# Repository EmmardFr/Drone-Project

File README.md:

# Drone-Project

- `hardware/` contains hardware design files:
  - `Datasheets/`: component datasheets (IMUs, barometers, and related parts) used during hardware selection.
  - `Graphics/`: project graphics and visual assets.
  - `Schematics/`: standalone schematic libraries/references for key components (e.g., sensors and Teensy 4.1).
  - PCB designs, in development order:
    1. `ismd_flight_computer (obselete)/` (deprecated early prototype): initial all-in-one flight-computer concept combining Teensy 4.1, multiple IMU/barometer options, and onboard power circuitry.
    2. `ismd_fc_sensortest/`: dedicated sensor test board used to compare multiple IMU and barometer options around a Teensy 4.1 base.
    3. `Carrier_PCB/`: first carrier board revision for system integration (power distribution, receiver I/O, ESC/motor signal breakout, and module connectors).
    4. `Carrier_PCB_v2/`: second carrier board revision refining the carrier design and production-ready outputs.
- `software/` contains firmware, libraries, and software tooling.

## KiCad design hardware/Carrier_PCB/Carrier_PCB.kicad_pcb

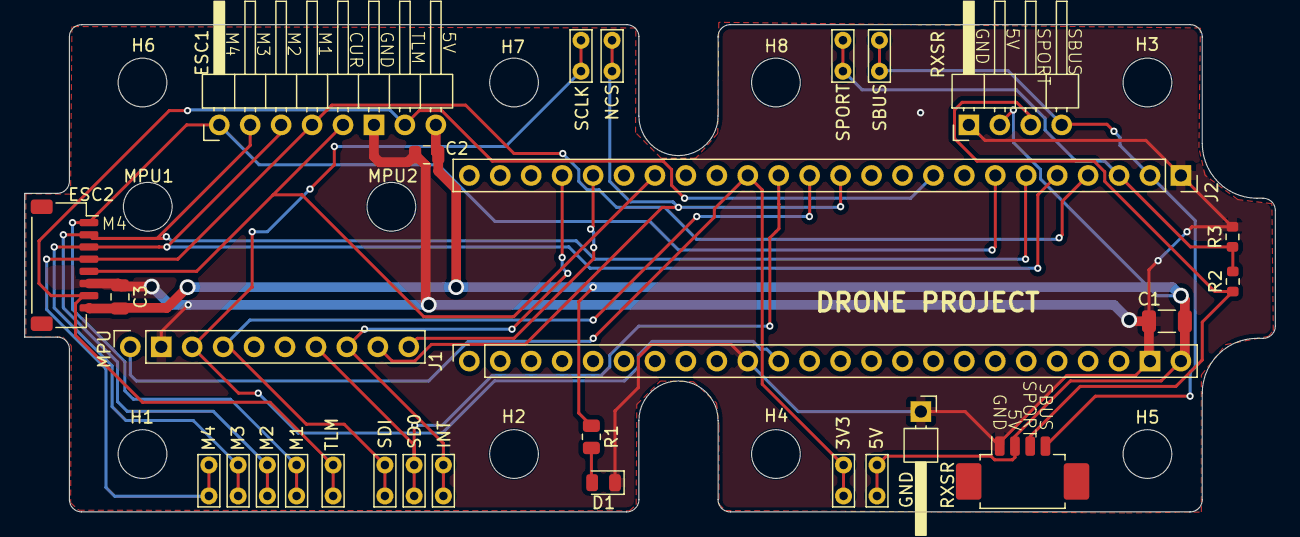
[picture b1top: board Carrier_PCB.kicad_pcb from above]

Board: 2 copper layers, 102.7 x 40.0 mm, 39 parts (0 on the bottom side), 19 nets.

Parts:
3V3, 5V: TestPoint; TestPoint_Bridge_Pitch2.54mm_Drill0.7mm
C1: 10u; C_1206_3216Metric
C2, C3: 100n; C_0805_2012Metric
D1: LED; LED_0805_2012Metric
ESC1: Conn_01x08; PinHeader_1x08_P2.54mm_Horizontal
ESC2: Conn_01x08; JST_SH_SM08B-SRSS-TB_1x08-1MP_P1.00mm_Horizontal
GND: Conn_01x01; PinHeader_1x01_P2.54mm_Horizontal
H1, H2, H3, H4, H5, H6, H7, H8: MountingHole; MountingHole_4mm
INT: TestPoint; TestPoint_Bridge_Pitch2.54mm_Drill0.7mm
J1, J2: Conn_01x24; PinSocket_1x24_P2.54mm_Vertical
M1, M2, M3, M4: TestPoint; TestPoint_Bridge_Pitch2.54mm_Drill0.7mm
MPU: Conn_01x10; PinSocket_1x10_P2.54mm_Vertical
MPU1, MPU2: MountingHole; MountingHole_4mm
NCS: TestPoint; TestPoint_Bridge_Pitch2.54mm_Drill0.7mm
R1: 300; R_0805_2012Metric
R2: 10K; R_0603_1608Metric
R3: 20K; R_0603_1608Metric
RXSR: Conn_01x04; PinHeader_1x04_P2.54mm_Horizontal
RXSR#2: Conn_01x04; Molex_PicoBlade_53261-0471_1x04-1MP_P1.25mm_Horizontal
SBUS: TestPoint; TestPoint_Bridge_Pitch2.54mm_Drill0.7mm
SCLK: TestPoint; TestPoint_Bridge_Pitch2.54mm_Drill0.7mm
SD0: TestPoint; TestPoint_Bridge_Pitch2.54mm_Drill0.7mm
SDI: TestPoint; TestPoint_Bridge_Pitch2.54mm_Drill0.7mm
SPORT: TestPoint; TestPoint_Bridge_Pitch2.54mm_Drill0.7mm
TLM: TestPoint; TestPoint_Bridge_Pitch2.54mm_Drill0.7mm

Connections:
+3.3V: 3V3.1 (1_1), J2.15, MPU.1
+5V: 5V.1 (1_1), C1.1, C2.2, C3.2, ESC1.8, ESC2.8, J1.24, R1.1, RXSR.2, RXSR#2.2
GND: C1.2, C2.1, C3.1, D1.1 (K), ESC1.6, ESC2.6, GND.1 (Pin_1_1), J1.10, J1.23, J2.1, MPU.2, R3.2, RXSR.1, RXSR#2.1
unnamed: D1.2 (A), R1.2
unnamed: J1.11, MPU.3, SCLK.1 (1_1)
unnamed: J2.2, RXSR.4, RXSR#2.4, SBUS.1 (1_1)
unnamed: ESC1.4, ESC2.4, J2.4, M4.1 (1_1)
unnamed: ESC1.3, ESC2.3, J2.5, M3.1 (1_1)
unnamed: ESC1.2, ESC2.2, J2.6, M2.1 (1_1)
unnamed: ESC1.1, ESC2.1, J2.7, M1.1 (1_1)
unnamed: ESC1.7, ESC2.7, J2.9, TLM.1 (1_1)
unnamed: J2.12, MPU.9, NCS.1 (1_1)
unnamed: J2.13, MPU.4, SDI.1 (1_1)
unnamed: J2.14, MPU.7, SD0.1 (1_1)
unnamed: ESC1.5, ESC2.5, J2.18
unnamed: J2.20, MPU.10
unnamed: INT.1 (1_1), J2.21, MPU.8
SPORT_MCU: J2.3, R2.2, R3.1, SPORT.1 (1_1)
SPORT_RX: R2.1, RXSR.3, RXSR#2.3

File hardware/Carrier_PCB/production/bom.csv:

Designator,Footprint,Quantity,Value,LCSC Part #
"3V3, 5V, INT, M1, M2, M3, M4, NCS, SBUS, SCLK, SD0, SDI, SPORT, TLM",TestPoint_Bridge_Pitch2.54mm_Drill0.7mm,14,TestPoint,
C1,1206,1,10u,
"C2, C3",0805,2,100n,
D1,0805,1,LED,
ESC1,PinHeader_1x08_P2.54mm_Horizontal,1,Conn_01x08,
ESC2,JST_SH_SM08B-SRSS-TB_1x08-1MP_P1.00mm_Horizontal,1,Conn_01x08,
GND,PinHeader_1x01_P2.54mm_Horizontal,1,Conn_01x01,
"J1, J2",PinSocket_1x24_P2.54mm_Vertical,2,Conn_01x24,
MPU,PinSocket_1x10_P2.54mm_Vertical,1,Conn_01x10,
R1,0805,1,300,
R2,0603,1,10K,
R3,0603,1,20K,
RXSR_2,Molex_PicoBlade_53261-0471_1x04-1MP_P1.25mm_Horizontal,1,Conn_01x04,
RXSR,PinHeader_1x04_P2.54mm_Horizontal,1,Conn_01x04,

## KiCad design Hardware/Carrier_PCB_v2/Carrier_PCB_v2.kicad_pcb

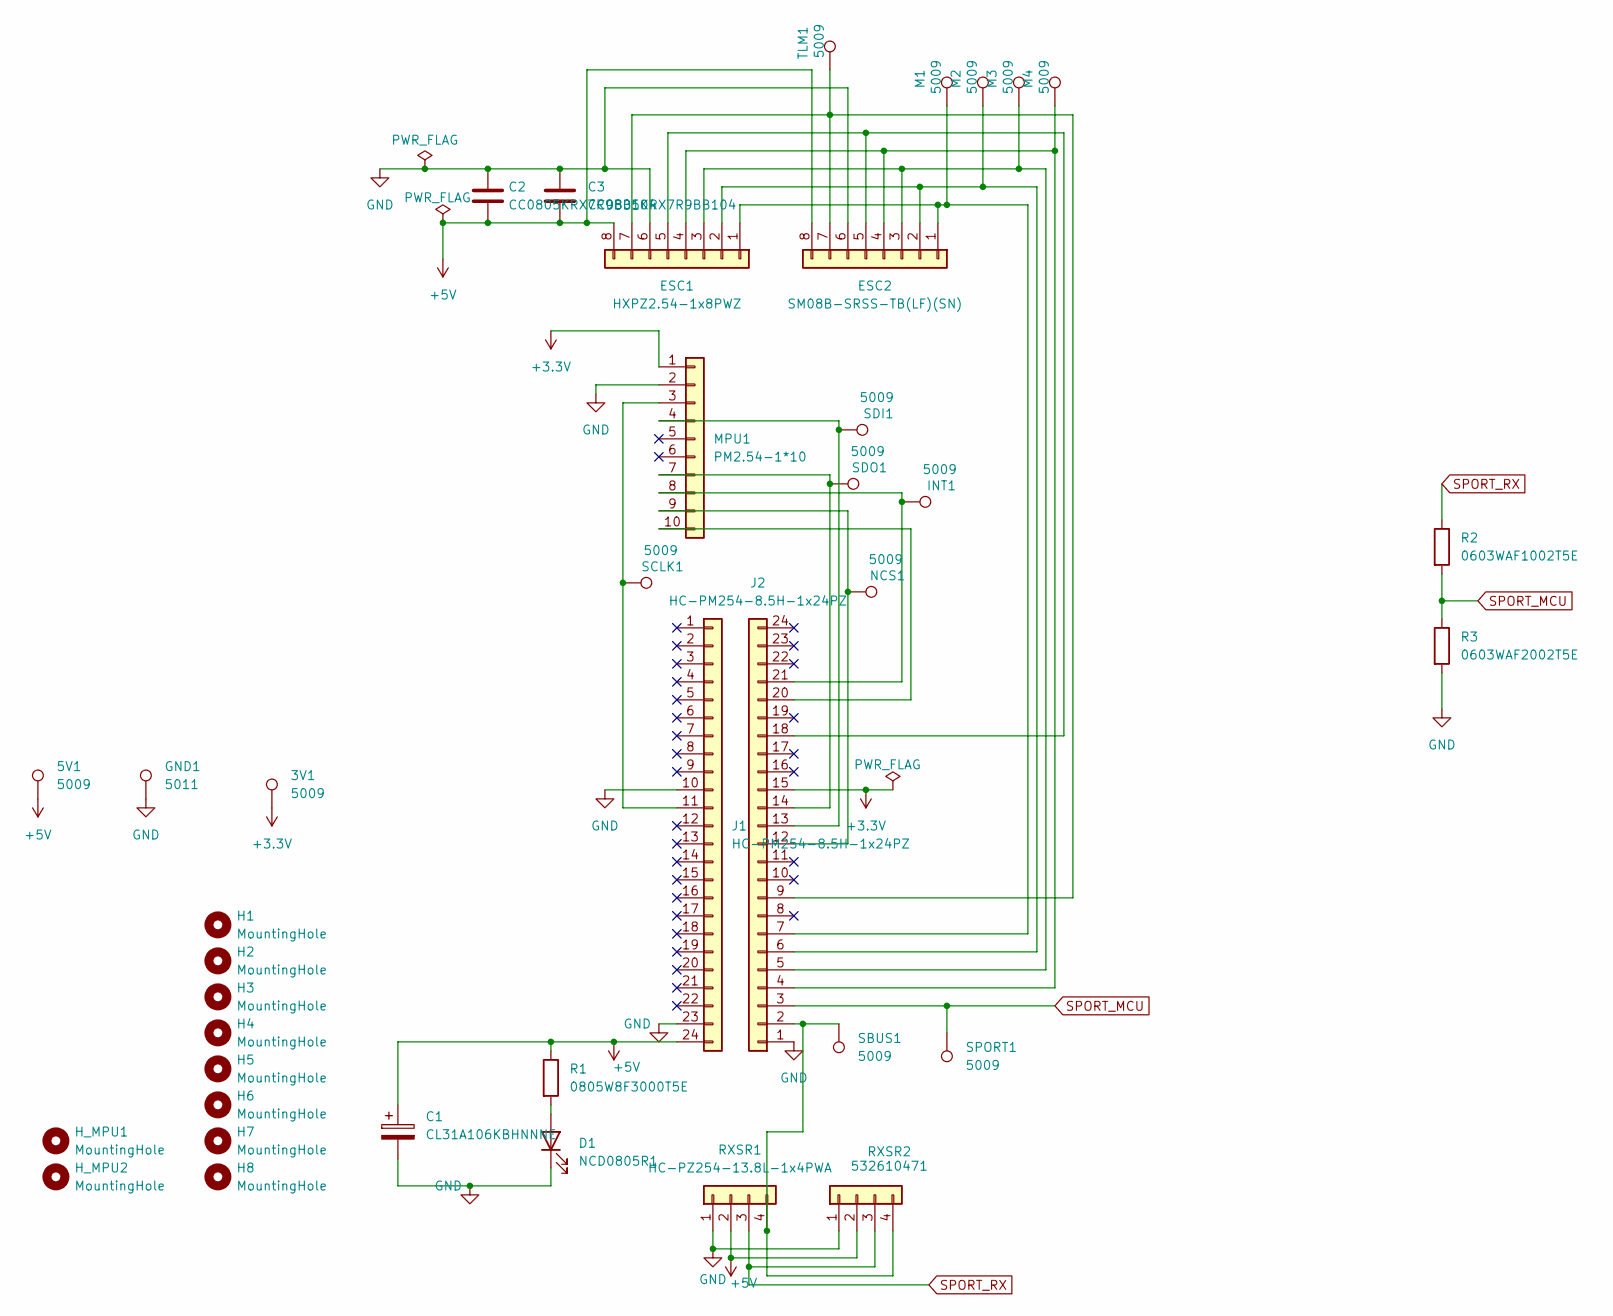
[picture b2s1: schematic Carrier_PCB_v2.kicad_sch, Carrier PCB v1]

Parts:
3V1, 5V1: 5009; TestPoint_Keystone_5005-5009_Compact
C1: CL31A106KBHNNNE; C_1206_3216Metric
C2, C3: CC0805KRX7R9BB104; C_0805_2012Metric
D1: NCD0805R1; LED_0805_2012Metric
ESC1: HXPZ2.54-1x8PWZ; PinHeader_1x08_P2.54mm_Horizontal
ESC2: SM08B-SRSS-TB(LF)(SN); JST_SH_SM08B-SRSS-TB_1x08-1MP_P1.00mm_Horizontal
GND1: 5011; TestPoint_Keystone_5010-5014_Multipurpose
H1, H2, H3, H4, H5, H6, H7, H8: MountingHole; MountingHole_4mm
H_MPU1, H_MPU2: MountingHole; MountingHole_4mm
INT1: 5009; TestPoint_Keystone_5005-5009_Compact
J1, J2: HC-PM254-8.5H-1x24PZ; PinSocket_1x24_P2.54mm_Vertical
M1, M2, M3, M4: 5009; TestPoint_Keystone_5005-5009_Compact
MPU1: PM2.54-1*10; PinSocket_1x10_P2.54mm_Vertical
NCS1: 5009; TestPoint_Keystone_5005-5009_Compact
R1: 0805W8F3000T5E; R_0805_2012Metric
R2: 0603WAF1002T5E; R_0603_1608Metric
R3: 0603WAF2002T5E; R_0603_1608Metric
RXSR1: HC-PZ254-13.8L-1x4PWA; PinHeader_1x04_P2.54mm_Horizontal
RXSR2: 532610471; Molex_PicoBlade_53261-0471_1x04-1MP_P1.25mm_Horizontal
SBUS1: 5009; TestPoint_Keystone_5005-5009_Compact
SCLK1: 5009; TestPoint_Keystone_5005-5009_Compact
SDI1: 5009; TestPoint_Keystone_5005-5009_Compact
SDO1: 5009; TestPoint_Keystone_5005-5009_Compact
SPORT1: 5009; TestPoint_Keystone_5005-5009_Compact
TLM1: 5009; TestPoint_Keystone_5005-5009_Compact

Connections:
+3.3V: 3V1.1 (1_1), J2.15, MPU1.1
+5V: 5V1.1 (1_1), C1.1, C2.2, C3.2, ESC1.8, ESC2.8, J1.24, R1.1, RXSR1.2, RXSR2.2
GND: C1.2, C2.1, C3.1, D1.1 (K), ESC1.6, ESC2.6, GND1.1 (1_1), J1.10, J1.23, J2.1, MPU1.2, R3.2, RXSR1.1, RXSR2.1
unnamed: D1.2 (A), R1.2
unnamed: ESC1.1, ESC2.1, J2.7, M1.1 (1_1)
unnamed: ESC1.2, ESC2.2, J2.6, M2.1 (1_1)
unnamed: ESC1.3, ESC2.3, J2.5, M3.1 (1_1)
unnamed: ESC1.4, ESC2.4, J2.4, M4.1 (1_1)
unnamed: ESC1.5, ESC2.5, J2.18
unnamed: ESC1.7, ESC2.7, J2.9, TLM1.1 (1_1)
unnamed: J1.11, MPU1.3, SCLK1.1 (1_1)
unnamed: J2.2, RXSR1.4, RXSR2.4, SBUS1.1 (1_1)
unnamed: J2.12, MPU1.9, NCS1.1 (1_1)
unnamed: J2.13, MPU1.4, SDI1.1 (1_1)
unnamed: J2.14, MPU1.7, SDO1.1 (1_1)
unnamed: J2.20, MPU1.10
unnamed: INT1.1 (1_1), J2.21, MPU1.8
SPORT_MCU: J2.3, R2.2, R3.1, SPORT1.1 (1_1)
SPORT_RX: R2.1, RXSR1.3, RXSR2.3

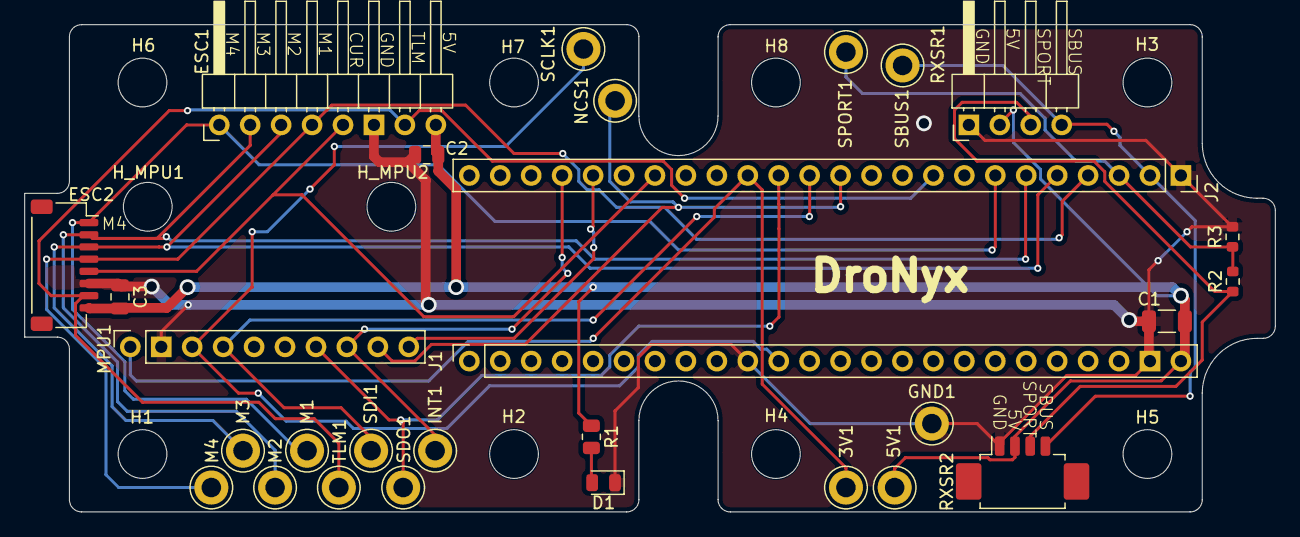
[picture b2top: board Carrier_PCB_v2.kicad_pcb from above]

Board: 2 copper layers, 102.7 x 40.0 mm, 39 parts (0 on the bottom side), 19 nets.

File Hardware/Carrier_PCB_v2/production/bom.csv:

Designator,Footprint,Quantity,Value,LCSC Part #
"3V1, 5V1, INT1, M1, M2, M3, M4, NCS1, SBUS1, SCLK1, SDI1, SDO1, SPORT1, TLM1",TestPoint_Keystone_5005-5009_Compact,14,5009,
C1,1206,1,CL31A106KBHNNNE,
"C2, C3",0805,2,CC0805KRX7R9BB104,
D1,0805,1,NCD0805R1,
ESC1,PinHeader_1x08_P2.54mm_Horizontal,1,HXPZ2.54-1x8PWZ,
ESC2,JST_SH_SM08B-SRSS-TB_1x08-1MP_P1.00mm_Horizontal,1,SM08B-SRSS-TB(LF)(SN),
GND1,TestPoint_Keystone_5010-5014_Multipurpose,1,5011,
"J1, J2",PinSocket_1x24_P2.54mm_Vertical,2,HC-PM254-8.5H-1x24PZ,
MPU1,PinSocket_1x10_P2.54mm_Vertical,1,PM2.54-1*10,
R1,0805,1,0805W8F3000T5E,
R2,0603,1,0603WAF1002T5E,
R3,0603,1,0603WAF2002T5E,
RXSR1,PinHeader_1x04_P2.54mm_Horizontal,1,HC-PZ254-13.8L-1x4PWA,
RXSR2,Molex_PicoBlade_53261-0471_1x04-1MP_P1.25mm_Horizontal,1,532610471,

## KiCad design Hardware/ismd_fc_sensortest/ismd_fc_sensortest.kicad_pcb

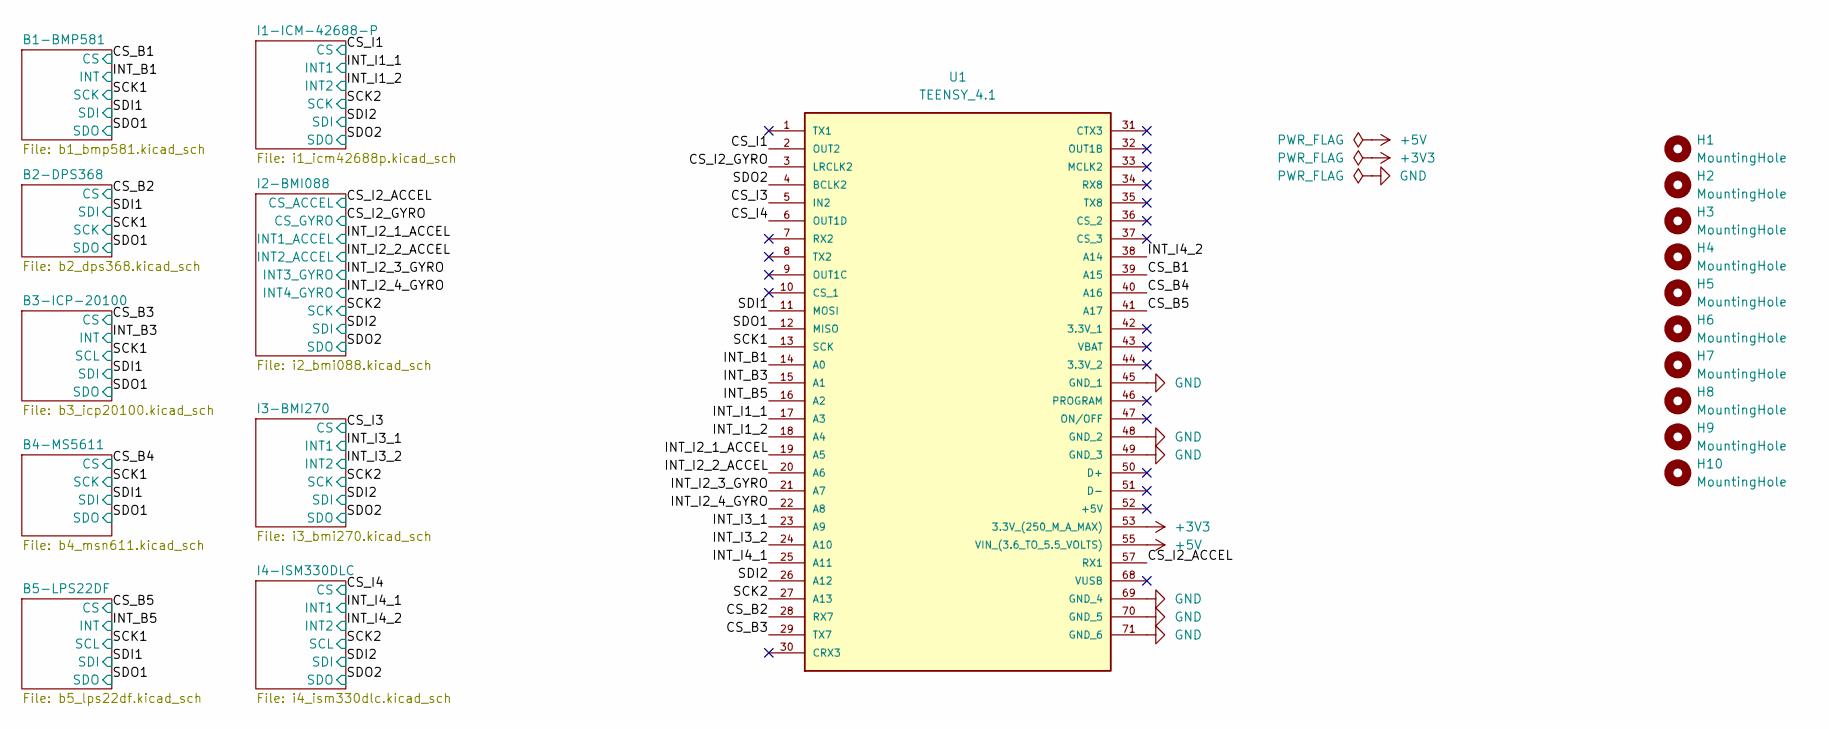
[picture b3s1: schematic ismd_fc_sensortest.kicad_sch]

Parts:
H1, H2, H3, H4, H5, H6, H7, H8, H9, H10: MountingHole; MountingHole_4mm
U1: TEENSY_4.1; TEENSY41; Manufacturer_Part_Number TEENSY 4.1

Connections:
+3V3: U1.53 (3.3V_(250_M_A_MAX)); also elsewhere on the board
+5V: U1.55 (VIN_(3.6_TO_5.5_VOLTS))
/CS_B1: U1.39 (A15); also elsewhere on the board
/CS_B2: U1.28 (RX7); also elsewhere on the board
/CS_B3: U1.29 (TX7); also elsewhere on the board
/CS_B4: U1.40 (A16); also elsewhere on the board
/CS_B5: U1.41 (A17); also elsewhere on the board
/CS_I1: U1.2 (OUT2); also elsewhere on the board
/CS_I2_ACCEL: U1.57 (RX1); also elsewhere on the board
/CS_I2_GYRO: U1.3 (LRCLK2); also elsewhere on the board
/CS_I3: U1.5 (IN2); also elsewhere on the board
/CS_I4: U1.6 (OUT1D); also elsewhere on the board
/INT_B1: U1.14 (A0); also elsewhere on the board
/INT_B3: U1.15 (A1); also elsewhere on the board
/INT_B5: U1.16 (A2); also elsewhere on the board
/INT_I1_1: U1.17 (A3); also elsewhere on the board
/INT_I1_2: U1.18 (A4); also elsewhere on the board
/INT_I2_1_ACCEL: U1.19 (A5); also elsewhere on the board
/INT_I2_2_ACCEL: U1.20 (A6); also elsewhere on the board
/INT_I2_3_GYRO: U1.21 (A7); also elsewhere on the board
/INT_I2_4_GYRO: U1.22 (A8); also elsewhere on the board
/INT_I3_1: U1.23 (A9); also elsewhere on the board
/INT_I3_2: U1.24 (A10); also elsewhere on the board
/INT_I4_1: U1.25 (A11); also elsewhere on the board
/INT_I4_2: U1.38 (A14); also elsewhere on the board
/SCK1: U1.13 (SCK); also elsewhere on the board
/SCK2: U1.27 (A13); also elsewhere on the board
/SDI1: U1.11 (MOSI); also elsewhere on the board
/SDI2: U1.26 (A12); also elsewhere on the board
/SDO1: U1.12 (MISO); also elsewhere on the board
/SDO2: U1.4 (BCLK2); also elsewhere on the board
GND: U1.45 (GND_1), U1.48 (GND_2), U1.49 (GND_3), U1.69 (GND_4), U1.70 (GND_5), U1.71 (GND_6); also elsewhere on the board

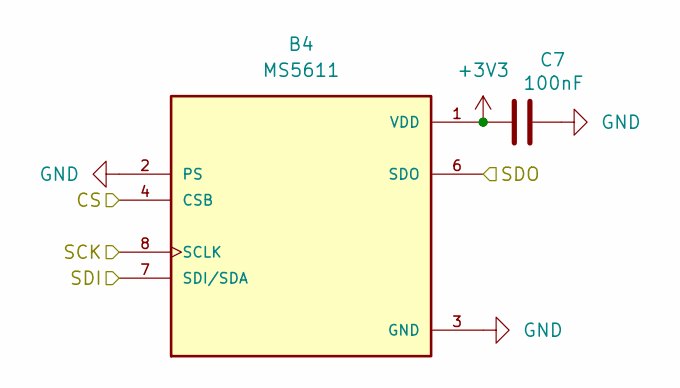
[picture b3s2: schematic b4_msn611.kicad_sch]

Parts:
B4: MS5611; SON125P500X300X100-8N; PARTREV 06/2017
C7: 100nF; C_0201_0603Metric

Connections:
+3V3: B4.1 (VDD), C7.2; also elsewhere on the board
/CS_B4: B4.4 (CSB), B4.5 (CSB); also elsewhere on the board
/SCK1: B4.8 (SCLK); also elsewhere on the board
/SDI1: B4.7 (SDI/SDA); also elsewhere on the board
/SDO1: B4.6 (SDO); also elsewhere on the board
GND: B4.2 (PS), B4.3 (GND), C7.1; also elsewhere on the board

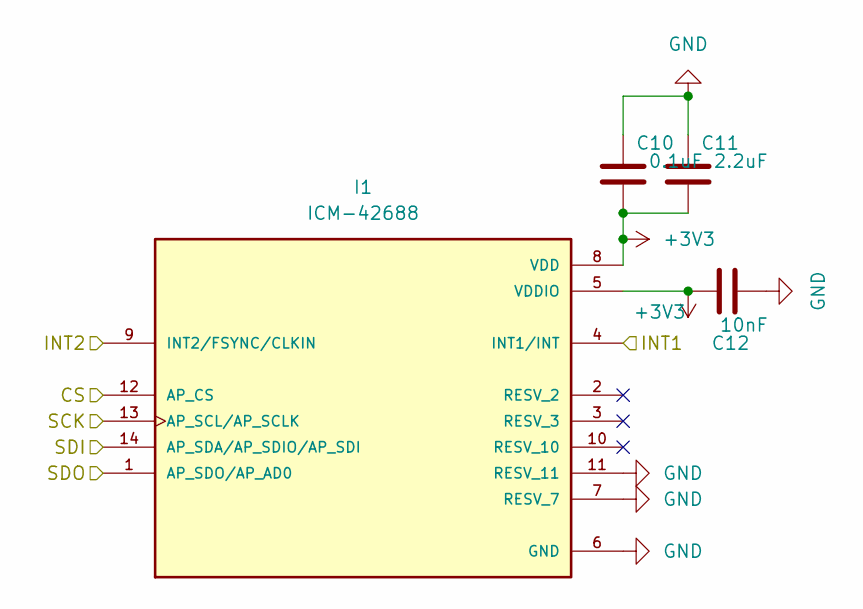
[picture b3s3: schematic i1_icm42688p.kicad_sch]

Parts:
C10: 0.1uF; C_0201_0603Metric
C11: 2.2uF; C_0201_0603Metric
C12: 10nF; C_0201_0603Metric
I1: ICM-42688; PQFN50P300X250X97-14N; PARTREV 1.2

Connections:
+3V3: C10.2, C11.2, C12.1, I1.5 (VDDIO), I1.8 (VDD); also elsewhere on the board
/CS_I1: I1.12 (AP_CS); also elsewhere on the board
/INT_I1_1: I1.4 (INT1/INT); also elsewhere on the board
/INT_I1_2: I1.9 (INT2/FSYNC/CLKIN); also elsewhere on the board
/SCK2: I1.13 (AP_SCL/AP_SCLK); also elsewhere on the board
/SDI2: I1.14 (AP_SDA/AP_SDIO/AP_SDI); also elsewhere on the board
/SDO2: I1.1 (AP_SDO/AP_AD0); also elsewhere on the board
GND: C10.1, C11.1, C12.2, I1.6 (GND), I1.7 (RESV_7), I1.11 (RESV_11); also elsewhere on the board

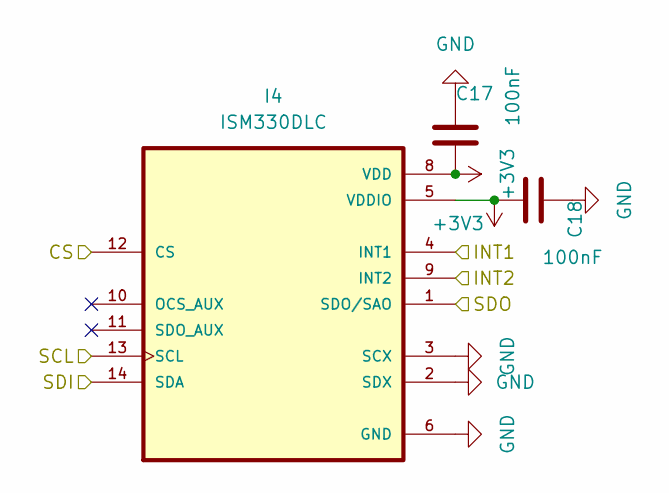
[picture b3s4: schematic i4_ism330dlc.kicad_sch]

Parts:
C17, C18: 100nF; C_0201_0603Metric
I4: ISM330DLC; PQFN50P250X300X86-14N; PARTREV 2

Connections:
+3V3: C17.1, C18.1, I4.5 (VDDIO), I4.8 (VDD); also elsewhere on the board
/CS_I4: I4.12 (CS); also elsewhere on the board
/INT_I4_1: I4.4 (INT1); also elsewhere on the board
/INT_I4_2: I4.9 (INT2); also elsewhere on the board
/SCK2: I4.13 (SCL); also elsewhere on the board
/SDI2: I4.14 (SDA); also elsewhere on the board
/SDO2: I4.1 (SDO/SAO); also elsewhere on the board
GND: C17.2, C18.2, I4.2 (SDX), I4.3 (SCX), I4.6 (GND), I4.7 (GND); also elsewhere on the board

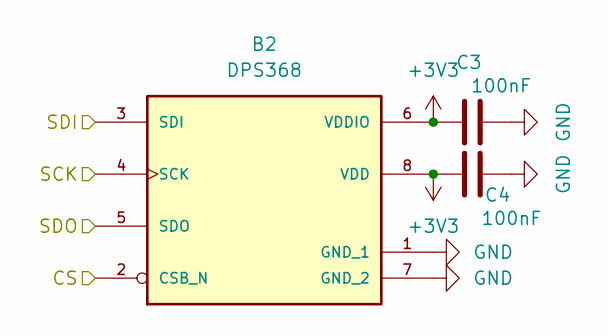
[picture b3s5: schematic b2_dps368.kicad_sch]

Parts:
B2: DPS368; LGA8S145X65P2X4_200X250X110-V
C3, C4: 100nF; C_0201_0603Metric

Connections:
+3V3: B2.6 (VDDIO), B2.8 (VDD), C3.1, C4.1; also elsewhere on the board
/CS_B2: B2.2 (CSB_N); also elsewhere on the board
/SCK1: B2.4 (SCK); also elsewhere on the board
/SDI1: B2.3 (SDI); also elsewhere on the board
/SDO1: B2.5 (SDO); also elsewhere on the board
GND: B2.1 (GND_1), B2.7 (GND_2), C3.2, C4.2; also elsewhere on the board

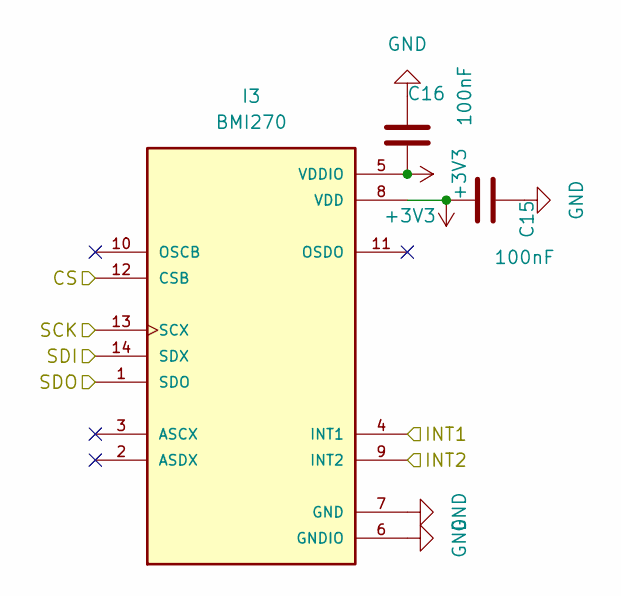
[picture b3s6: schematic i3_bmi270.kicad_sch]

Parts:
C15, C16: 100nF; C_0201_0603Metric
I3: BMI270; XDCR_BMI270

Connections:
+3V3: C15.1, C16.1, I3.5 (VDDIO), I3.8 (VDD); also elsewhere on the board
/CS_I3: I3.12 (CSB); also elsewhere on the board
/INT_I3_1: I3.4 (INT1); also elsewhere on the board
/INT_I3_2: I3.9 (INT2); also elsewhere on the board
/SCK2: I3.13 (SCX); also elsewhere on the board
/SDI2: I3.14 (SDX); also elsewhere on the board
/SDO2: I3.1 (SDO); also elsewhere on the board
GND: C15.2, C16.2, I3.6 (GNDIO), I3.7 (GND); also elsewhere on the board

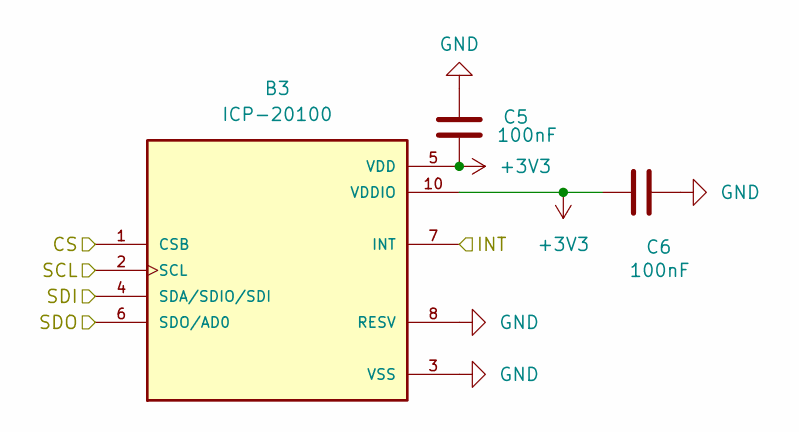
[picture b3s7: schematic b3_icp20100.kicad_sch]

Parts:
B3: ICP-20100; PQFN50P200X200X85-10N; PARTREV 1.1
C5, C6: 100nF; C_0201_0603Metric

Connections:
+3V3: B3.5 (VDD), B3.10 (VDDIO), C5.2, C6.2; also elsewhere on the board
/CS_B3: B3.1 (CSB); also elsewhere on the board
/INT_B3: B3.7 (INT); also elsewhere on the board
/SCK1: B3.2 (SCL); also elsewhere on the board
/SDI1: B3.4 (SDA/SDIO/SDI); also elsewhere on the board
/SDO1: B3.6 (SDO/AD0); also elsewhere on the board
GND: B3.3 (VSS), B3.8 (RESV), B3.9 (RESV), C5.1, C6.1; also elsewhere on the board

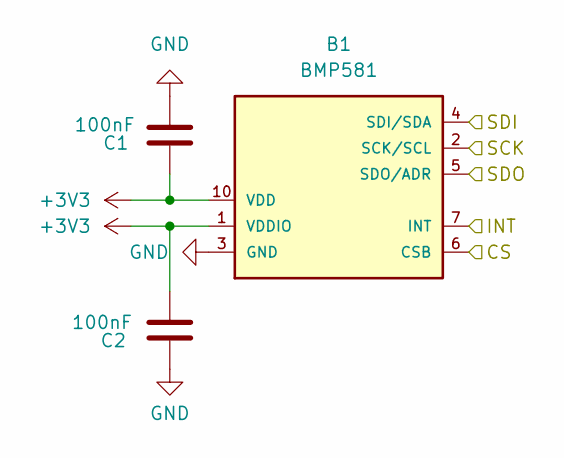
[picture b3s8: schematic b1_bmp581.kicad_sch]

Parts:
B1: BMP581
C1, C2: 100nF; C_0201_0603Metric

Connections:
+3V3: B1.1 (VDDIO), B1.10 (VDD), C1.1, C2.2; also elsewhere on the board
/CS_B1: B1.6 (CSB); also elsewhere on the board
/INT_B1: B1.7 (INT); also elsewhere on the board
/SCK1: B1.2 (SCK/SCL); also elsewhere on the board
/SDI1: B1.4 (SDI/SDA); also elsewhere on the board
/SDO1: B1.5 (SDO/ADR); also elsewhere on the board
GND: B1.3 (GND), B1.8 (GND), B1.9 (GND), C1.2, C2.1; also elsewhere on the board

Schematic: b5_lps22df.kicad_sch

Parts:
B5: LPS22DF; ST_HLGA-10_2x2mm_P0.5mm_LayoutBorder3x2y
C8, C9: 100nF; C_0402_1005Metric

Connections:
+3V3: B5.1 (Vdd_IO), B5.10 (VDD), C8.2, C9.2; also elsewhere on the board
/CS_B5: B5.6 (~CS); also elsewhere on the board
/INT_B5: B5.7 (INT_DRDY); also elsewhere on the board
/SCK1: B5.2 (SCL); also elsewhere on the board
/SDI1: B5.4 (SDA); also elsewhere on the board
/SDO1: B5.5 (SA0); also elsewhere on the board
GND: B5.3 (GND), B5.8 (GND_IO), B5.9 (GND), C8.1, C9.1; also elsewhere on the board

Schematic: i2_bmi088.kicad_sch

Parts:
C13, C14: 100nF; C_0402_1005Metric
I2: BMI088; Bosch_LGA-16_4.5x3mm_P0.5mm_LayoutBorder7x1y_ClockwisePinNu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

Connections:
+3V3: C13.1, C14.1, I2.3 (VDD), I2.11 (VDDIO); also elsewhere on the board
/CS_I2_ACCEL: I2.14 (~CSB1); also elsewhere on the board
/CS_I2_GYRO: I2.5 (~CSB2); also elsewhere on the board
/INT_I2_1_ACCEL: I2.16 (INT1); also elsewhere on the board
/INT_I2_2_ACCEL: I2.1 (INT2); also elsewhere on the board
/INT_I2_3_GYRO: I2.12 (INT3); also elsewhere on the board
/INT_I2_4_GYRO: I2.13 (INT4); also elsewhere on the board
/SCK2: I2.8 (SCK/SCL); also elsewhere on the board
/SDI2: I2.9 (SDI/SDA); also elsewhere on the board
/SDO2: I2.10 (SDO2), I2.15 (SDO1); also elsewhere on the board
GND: C13.2, C14.2, I2.2 (GNDA), I2.4 (GNDA), I2.6 (GNDIO), I2.7 (PS); also elsewhere on the board

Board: 2 copper layers, 36 parts (0 on the bottom side), 31 nets, no tracks yet.

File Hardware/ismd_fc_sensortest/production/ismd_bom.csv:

Designator,Footprint,Quantity,Value,LCSC Part #
B1,BMP581,1,BMP581,
B2,LGA8S145X65P2X4_200X250X110-V,1,DPS368,
B3,PQFN50P200X200X85-10N,1,ICP-20100,
B4,SON125P500X300X100-8N,1,MS5611,
B5,ST_HLGA-10_2x2mm_P0.5mm_LayoutBorder3x2y,1,LPS22DF,
"C1, C13, C14, C15, C16, C17, C18, C2, C3, C4, C5, C6, C7, C8, C9",0402,15,100nF,
C10,0402,1,0.1uF,
C11,0402,1,2.2uF,
C12,0402,1,10nF,
I1,PQFN50P300X250X97-14N,1,ICM-42688,
I2,Bosch_LGA-16_4.5x3mm_P0.5mm_LayoutBorder7x1y_ClockwisePinNumbering,1,BMI088,
I3,XDCR_BMI270,1,BMI270,
I4,PQFN50P250X300X86-14N,1,ISM330DLC,
U1,TEENSY41,1,TEENSY 4.1,

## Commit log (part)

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2026-06-10 change gyro DLPF config
2026-06-11 Implement rx communication. However, it introduces almost 3ms of delay...
2026-06-12 Implement rx
2026-06-12 Eliminate the 3ms delay when reading rx
2026-06-13 rx_gyro_v1.3 is the latest and now works reliably.
2026-06-15 pid_esc_rx_gyro code is ready to fly. PID tuning remaining.
2026-06-21 PCB first version. Not wired yet
2026-06-22 Update PCB. Not wired yet
